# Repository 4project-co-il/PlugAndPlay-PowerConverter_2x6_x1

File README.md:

# PlugAndPlay: Power Converter for Pololu's D42V55Fx and D36V50Fx voltage regulator modules
This is the repository with the files for PlugAndPlay power converter board.

The board has 2x PnP power module ports and one connector for Pololu's D42V55Fx or D36V50Fx voltage regulator module.
One PnP power module port is used as an input, another as an output and the connector allows pluging in one of the Pololu's voltage regulators from D42V55Fx or D36V50Fx families.

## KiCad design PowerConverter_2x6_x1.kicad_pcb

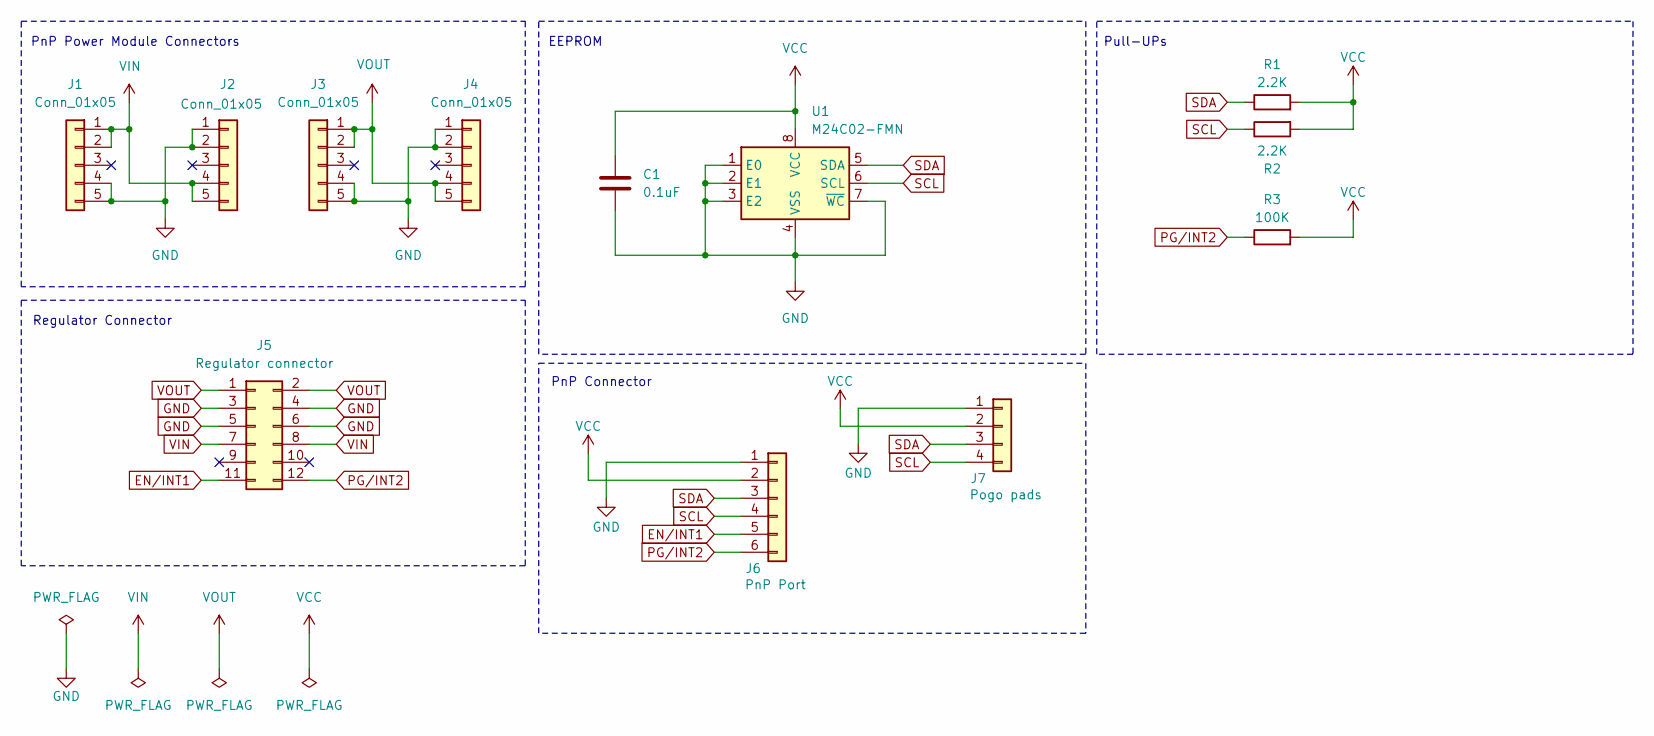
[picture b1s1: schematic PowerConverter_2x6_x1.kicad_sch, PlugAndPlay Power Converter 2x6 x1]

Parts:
C1: 0.1uF; C_0603_1608Metric; MPN C14663
J1, J3: Conn_01x05; PinSocket_1x05_P2.54mm_Vertical_SMD_Pin1Right; MPN RealRun
J2, J4: Conn_01x05; PinSocket_1x05_P2.54mm_Vertical_SMD_Pin1Left; MPN RealRun
J5: Regulator connector; PinSocket_2x06_P2.54mm_Vertical_SMD
J6: JST_SH_SM06B-SRSS-TB_1x06-1MP_P1.00mm_Horizontal; MPN C7430448
J7: Conn_01x04; PogoPinsPads_1x04_P2.5mm
R1, R2: 2.2K; R_0603_1608Metric; MPN C4190
R3: 100K; R_0603_1608Metric; MPN C25803
U1: M24C02-FMN; SOIC-8_3.9x4.9mm_P1.27mm; MPN C114502

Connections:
EN/INT1: J5.11, J6.5
GND: C1.2, J1.4, J1.5, J2.1, J2.2, J3.4, J3.5, J4.1, J4.2, J5.3, J5.4, J5.5, J5.6, J6.1, J7.1, U1.1 (E0), U1.2 (E1), U1.3 (E2), U1.4 (VSS), U1.7 (~WC)
PG/INT2: J5.12, J6.6, R3.1
SCL: J6.4, J7.4, R2.1, U1.6 (SCL)
SDA: J6.3, J7.3, R1.1, U1.5 (SDA)
VCC: C1.1, J6.2, J7.2, R1.2, R2.2, R3.2, U1.8 (VCC)
VIN: J1.1, J1.2, J2.4, J2.5, J5.7, J5.8
VOUT: J3.1, J3.2, J4.4, J4.5, J5.1, J5.2

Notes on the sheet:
PnP Power Module Connectors
Pull-UPs
Regulator Connector
PnP Connector
EEPROM

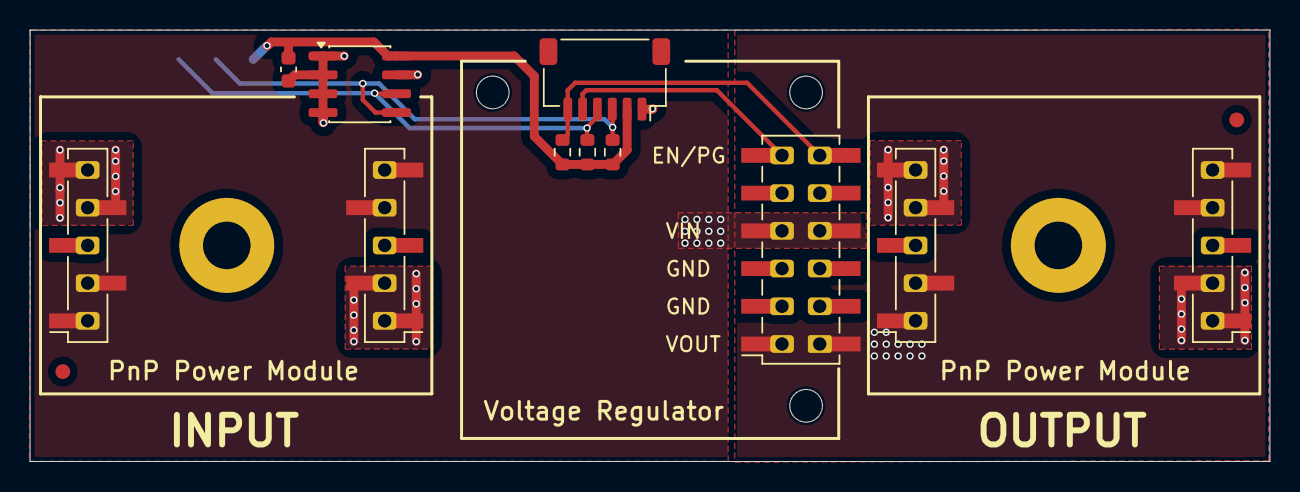
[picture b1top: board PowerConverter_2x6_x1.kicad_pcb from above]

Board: 2 copper layers, 83.5 x 29.0 mm, 12 parts (1 on the bottom side), 8 nets.
